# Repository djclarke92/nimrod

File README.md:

# Nimrod Home Automation

A home automation project based on the Raspberry Pi, Modbus IO devices and NodeMCU modules.  The control software is written in C++ and the web configuration is in PHP7.  Relies on 
a MySQL database running on a separate host.  The current software is compiled for Pi model B running the Rasbian buster release.

Why call it Nimrod ?  It needed a name and "Nimrod" was the name of a neanderthal butler in an early Doctor Who episode. The original purpose was to develop something to turn on my
motorbike glove heater 30 minutes before my morning alarm went off if the outside temperature was below 15 deg C.

The Nimrod software is compiled on your standard linux desktop PC, then cross compiled for the Pi version your are using.  In theory you could compile everything on the Pi and 
do away with the cross compiler step.

Uses dygraph.js from http://dygraphs.com for displaying graphs. Websocket support comes from https://libwebsockets.org/.

What can you do with it ?
* Input events can be switches, temperature values, voltage levels or time of day
* Turn on one or more output ports when an input event occurs
* Input switch events can be a click, double click or long click, each can trigger different output actions
* Input events can be chained together, e.g. if time is 6:30am and temperature sensor #2 is < 15 deg then turn on output #7 for 30 minutes
* Complex processes can be managed by the integratd PLC State Machine

Communication with each modbus device is polled.  All digital inputs are active low, i.e. connect to 0V / Gnd to activate.  All digital outputs are active low open collector outputs.

On a Pi4, we recommend that you move the /var file system onto a USB3 hard drive otherwise the Pi's uSDHC card will die quite soon due to the number of writes. 

The Nimrod web page also supports displaying CCTV camera images and video streams, to do this you need the mount the CCTV image storage filesystem onto the Pi (edit /etc/fstab and 
create /etc/.smbpwd).  The camera definitions are in the file/site_config.conf file.
1.	/etc/fstab example
	//<SERVER_IP_ADDRESS>/cctv  /cctv   cifs    auto,gid=users,file_mode=0660,dir_mode=0660,iocharset=utf8,credentials=/etc/.smbpwd  0 0
2.	/etc/.smbpwd example, mode must be 0600
	username=<some_user_name>
	password=<some_password>
	domain=YOURSMBWORKGROUP

Note that for each server using a guest account, you may wish to specify an additional share in /etc/samba/smb.conf
thus;

[cctv]
        comment = cctv
        inherit acls = Yes
        path = /cctv
        read only = No
        vfs objects =
[cctv2]
        comment = cctv2
        inherit acls = Yes
        path = /cctv
        read only = No
        vfs objects =

Add a share for each additional server that will connect using the same account. In /etc/fstab, specifiy the new share name for each additional server
//<SERVER_IP_ADDRESS/cctv2, etc

This works around some Windows/samba peculiarities and allows conflict-free file/directory access.

Alternatively, you could use NFS instead, if you aren't using Windows PC's to access the camera files.

## Devices, Device Info and IO Links

Each Modbus interface device is called a "Device" in Nimrod speak.  So a "Device" could be a 16 digital input unit, 8 relay output unit, 8 analog voltage input unit, etc.

Once you have define a device you need to tell Nimrod what each of it's ports is connected to, this is called the "Device Info".  So for a 16DI unit you would setup input channel 1 is 
"Kitchen switch 1", input channel 2 is "Lounge switch 1", etc. The actual connections are determined by the physical cabling between the switch and the Modbus device.  Output devices 
are similarly defined, e.g. 8RO device channel #4 is "Carport Lights".

Now that you have defined the inputs and outputs you need to tell Nimrod how to connect them together.  This is called "IO Links".  E.g. "Kitchen switch 1" links to 
"Carport Lights", and you can also specify if the output is on until the switch is pressed again or automatically turns off after a set time.

## Supported Modbus devices

Modbus RS485 devices from Wellpro and others

* WP3066ADAM		8DS18B20 - 8x DS18B20 temperature inputs
* WP3082ADAM		8AI - 8x 0-20mA / 4-20mA analog inputs
* WP3084ADAM		8VI - 8x 0-10V DC analog inputs
* WP8025ADAM		8RO - 8x relay outputs
* WP8026ADAM		16DI - 16x digital inputs
* WP8027ADAM		16DO - 16x digital outputs
* WP8028ADAM		8DI/8DO - 8x digital outputs, 8x digital inputs
* PD3064			8KT - 8 K Thermocouples
* HDL300			Submersible water level sensor

## Supported WiFi devices

* NodeMCU (ESP8266)
	modules - adc crypto enduser_setup file gpio http net node pwm tmr uart websocket wifi + TLS

# Nimrod package file structure
* ./LICENSE							GNU v3 license
* ./README.md						This file
* ./RELEASE-NOTES.TXT				A history of changes to Nimrod
* ./index.php						Nimrod web portal home page
* ./favicon.ico						Favicon file
* ./bin/nimrod						Nimrod server executable (amd64)
* ./bin/nimrod-arm7					Nimrod server executable (arm7)
* ./bin/set-address					Set the Modbus device index (amd64)
* ./bin/set-address-arm7			Set the Modbus device index (arm7)
* ./files/cameras.php				Shows CCTV camera snapshots on the Nimrod web console
* ./files/class.email.php
* ./files/common.php				Base configuration and some common functions
* ./files/commonhtml.php			Common functions which include HTML output.
* ./files/deviceinfo.php
* ./files/devices.php
* ./files/dygraph.js				Javascript graphing lib
* ./files/dygraph.css				Javascript graphing lib
* ./files/dygraph.min.js			Javascript graphing lib
* ./files/events.php				ToDo
* ./files/home.php
* ./files/intro.php					What is Nimrod
* ./files/monitor.php				Full screen monitor pages 1 and 2
* ./files/iolinks.php
* ./files/site_config.php
* ./files/site_config.php.sample	Example site config file
* ./files/styles.css
* ./images/*						Various image files to make Nimrod look good
* ./scripts/tables.sql				MySQL table creation sql script
* ./scripts/build-num.sh			Update the build number automatically each time makerelease.sh is run
* ./scripts/makerelease.sh			Create a new nimrod package
* ./scripts/nimrod.service			Exampe Nimrod service file of the Pi
* ./scripts/archive_cctv.sh			Script to delete old cctv files
* ./sounds/alerts.mp3
* ./sounds/warning1.mp3
* ./cctv -> /var/cctv				Symlink to your cctv images storage directory
* ./uploads							Create this directory manually and change the owner:group to www-data:www-data

# Raspberry Pi Model 4

## Create Pi bootable SD card

We recommend 16GB SD cards are used, an 8GB card is likely to run out of space in the future.

1.	umount /dev/sdd1
2.	dd bs=4M if=2019-07-10-raspbian-buster.img of=/dev/sdd
3.	boot the pi
	
## Initial Setup of the Pi

- Menu - Pi Configuration
	- System Tab
	- Expand Filesystem
	- Change password for pi user to something new (default is raspberry, nimrod default is passw0rd.23)
	- set hostname to nimrod (or nimrod2, nimrod3, etc)
	- Disable auto login 
- Interfaces Tab
	- Enable SSH
- Localization
	- Set Locale to EN / NZ
	- Set Timezone to Pacific/Auckland
	- Set Keyboard to United States / English International
	- Set WiFi Country to NZ
- Reboot
- Set password for root > sudu su; passwd
- Set static IP address
- sudo vi /etc/dhcpcd.conf (add to the end of the file)
		interface eth0
	  		static ip_address=192.168.1.199/24
	  		static routers=<your_gateway_ip_address>	
	  		static domain_name_servers=<dns_ip_addres_1> <dns_ip_address_2>
	  			(NZ InspireNet DNS servers are 203.114.168.2 203.114.128.2)
- Reboot	
- apt-get update
- apt-get upgrade
- Reboot

## Create the nimrod user on the Pi

It is recommended that you use the same uid/gid for each user/group across your installation. The useradd/groupadd 
commands have options for this.

1.	> adduser nimrod
	- Set password to something
2.	Add nimrod user to the dialout group to give acces to the /dev/ttyUSB* devices
	> adduser nimrod dialout
3.	Add any public ssh keys to $HOME/.ssh/authorized_keys
4.	Create pub/priv key pair
	> ssh-keygen -t rsa
	- copy the public key to nimrod@<database_server>:~/.ssh/authorized_keys

## Install additional packages required by Nimrod on the Pi

- cmd line: sudo apt-get update (update list of available packages)
- gui: sudo aptitude
- example to install curl
	- apt-cache search curl
	- apt-get install curl

Raspbian buster
- apache2 php.8.x-fpm php php-mysql php-gd
- libmodbus5 libmodbus-dev
- libssl-dev libusb-dev ntpddate
- mariadb-server
- mariadb-client libmariadb-dev
- (old mysql-client libmysqlclient-dev)
- msmtp msmtp-mta mailutils
- libwebsockets8 libwebsockets-dev libwebsockets-test-server
- gparted vsftpd

- Secure the mariadb installation
> sudo mysql_secure_installation

- Enable mod-ssl in apache using a self signed certificate
> sudo a2enmod ssl
> sudo a2ensite default-ssl
> sudo systemctl restart apache2

- Remove the default index.html file
> sudo rm /var/www/html/index.html

- make apache a member of the nimrod group
> sudo adduser www-data nimrod

## remove the swap file from the SD card

> sudo dphys-swapfile swapoff
> sudo dphys-swapfile uninstall
> sudo update-rc.d dphys-swapfile remove

## Move the /var directory onto a USB3 drive

- Once you transfer /var onto the USB3 drive the Pi will not boot without the USB3 drive connected
- Don't try and connect a second USB drive, the Pi4 can't cope with that
- Connect and the USB3 drive, format a large ext4 partition and a smaller swap partition
> sudo gparted

- Get the partition uuid's
> sudo blkid /dev/sda1
> sudo blkid /dev/sda2

- Edit the /etc/fstab to add in the new partitions
> sudo vi /etc/fstab
  # /dev/sda1
  PARTUUID=9ee98a25-97e4-xxxx-xxxx-dd0a23e1f247   swap    swap    defaults        0       0
  # /dev/sda2
  PARTUUID=51b819e6-8fd1-xxxx-xxxx-7ffbb871917e   /var    ext4    defaults        0       2
  
- Mount the new var partition and copy the files across
> sudo mount /dev/sda2 /mnt
> sudo rsync -axov /var/* /mnt

- Reboot and your /var partition and swap are on the USB3 drive
> sudo reboot

## Setup msmtp mail on the Pi

> sudo vi /etc/msmtprc
	# Set default values for all following accounts.
	defaults
	logfile /var/tmp/msmtp.log

	# Use the mail submission port 587 instead of the SMTP port 25.
	port 465

	# Always use TLS.
	tls on
	tls_starttls off

	# Set a list of trusted CAs for TLS. The default is to use system settings, but
	# you can select your own file.
	tls_trust_file /etc/ssl/certs/ca-certificates.crt

	# If you select your own file, you should also use the tls_crl_file command to
	# check for revoked certificates, but unfortunately getting revocation lists and
	# keeping them up to date is not straightforward.
	#tls_crl_file ~/.tls-crls

	# Mail account
	# TODO: Use the users username, e.g. root for system and pi for your raspbian user
	account pi

	# Host name of the SMTP server
	# TODO: Use the host of your own mail account
	host <your_isp_mail_host>

	# As an alternative to tls_trust_file/tls_crl_file, you can use tls_fingerprint
	# to pin a single certificate. You have to update the fingerprint when the
	# server certificate changes, but an attacker cannot trick you into accepting
	# a fraudulent certificate. Get the fingerprint with
	# $ msmtp --serverinfo --tls --tls-certcheck=off --host=smtp.freemail.example
	#tls_fingerprint 00:11:22:33:44:55:66:77:88:99:AA:BB:CC:DD:EE:FF:00:11:22:33
	
	# Envelope-from address
	# TODO: Use your own mail address
	from <pi_hostname>@<your_domain>
	
	# Authentication. The password is given using one of five methods, see below.
	auth on
	
	# TODO: Use your own user name for the mail account
	user pi@<your_domain>
	
	# Password method 1: Add the password to the system keyring, and let msmtp get
	# it automatically. To set the keyring password using Gnome's libsecret:
	# $ secret-tool store --label=msmtp \
	#   host smtp.freemail.example \
	#   service smtp \
	#   user joe.smith
	
	# Password method 2: Store the password in an encrypted file, and tell msmtp
	# which command to use to decrypt it. This is usually used with GnuPG, as in
	# this example. Usually gpg-agent will ask once for the decryption password.
	#passwordeval gpg2 --no-tty -q -d ~/.msmtp-password.gpg
	
	# Password method 3: Store the password directly in this file. Usually it is not
	# a good idea to store passwords in plain text files. If you do it anyway, at
	# least make sure that this file can only be read by yourself.
	# TODO: Use the password of your own mail account
	password <email_password>
	
	# Password method 4: Store the password in ~/.netrc. This method is probably not
	# relevant anymore.
	
	# Password method 5: Do not specify a password. Msmtp will then prompt you for
	# it. This means you need to be able to type into a terminal when msmtp runs.
	
	# Set a default account
	# TODO: Use the same account you've configured under account, e.g. root or pi
	account default: pi
	
	# Map local users to mail addresses (for crontab)
	aliases /etc/aliases
	
> sudo chown pi:pi /etc/msmtprc
> sudo chmod 0600 /etc/msmtprc
> sudo chmod 0777 /var/tmp
  cp /etc/msmtprc ~/.msmtprc

> sudo vi /etc/aliases
	root: pi@<your_domain>
	default: pi@<your_domain>
	
> sudo vi /etc/mail.rc
	set sendmail="/usr/bin/msmtp -t"

## Create a certificate so NodeMCU (ESP8266) WiFi devices can connect

> ssh nimrod@nimrod
> openssl req -x509 -nodes -days 3650 -newkey rsa:2048 -keyout nimrod-cert.key -out nimrod-cert.pem

# MySQL Database server

The MySQL database will contain the nimrod configuration and record events and monitoring data.
1.	Create nimrod user with password
2.	Create pub/priv key
	> ssh-keygen -t rsa
3.	Copy pub key to nimrod@pi
4.	Create nimrod database
5.	Create the nimrod tables
	
## Database username and password

If you want to change the default database username or password you need to edit the tables.sql and files/site_config.php files
to specify your required username and password before you create the tables. 
File:	./files/site_config.php			defines DB_USER_NAME and DB_PASSWORD
File:	./scripts/tables.sql			grant select,insert,update,delete on .......
	
## Database ssh tunnel

Nimrod sets up a tunnel to a remote mysql server as per the IP address in the site_config.php file. On the remote mysql host you need to add nimrod as a user and add 
the ssh keys for all nimrod hosts

# Installing Nimrod on the Pi into /var/www/html for the first time

1.	Copy the install tar file from your PC to the Pi
> scp nimrod-x.y.z.tgz nimrod@nimrod:/var/www/html/.
		
2.	Set permissions and untar the package as the nimrod user
> ssh nimrod@nimrod  
> sudo chown -R nimrod:nimrod /var/www/html  
> cd /var/www/html  
> tar xvzf nimrod.x.y.z.tgz  
> cp files/site_config.php.sample files/site_config.php  
> vi site_config.php  
	- set REMOTE_MYSQL_HOST and DB_PASSWORD
	
3.	Establish the SSH tunnel to the database host to accept the host key as the nimrod user
> ssh nimrod@REMOTE_DB_HOST  
> yes  
> ctrl-d		

4.	Create the guest user for camera ftp login
> adduser guest  
	- Set password to something (cameras will use guest/pwd to ftp videos to the server)
> add cctv symlink
	sudo su - guest
	cd /home/guest
	sudo mkdir /var/cctv .
	sudo mkdir /var/cctv/<camera_name>
	sudo chown -R guest:guest /var/cctv

4.	Apache2 setup
> Create the cctv symlink  
	cd /var/www/html  
	sudo ln -s /var/cctv cctv  
> Add apache to the guest group  
	sudo adduser www-data guest  
> Restart apache  
	sudo service apache2 restart

5.	Move the nimrod.log file onto /var/tmp
> cd /home/nimrod  
> sudo ln -s /var/tmp log  
> sudo vi /var/www/html/files/site_config.php
			
6.	Add nimrod to the guest group
> sudo adduser nimrod guest

7. create the web uploads directory
> sudo mkdir /var/www/html/uploads  
> sudo chown -R nimrod:nimrod /var/www/html  
> sudo chmod g+w /var/www/html/uploads

8.	Set nimrod to start automatically
> ssh pi@nimrod  
> cd /var/www/html  
> sudo cp scripts/nimrod.service.arm(7 or 64) /lib/systemd/system/nimrod.service  
> sudo chown root:root /lib/systemd/system/nimrod.service  
> sudo systemctl enable nimrod.service  
> sudo systemctl start nimrod

9.	Setup vsftpd if you have cameras attached so nimrod and apache can view the video files
> sudo vi /etc/vsftpd.conf  
  write_enable=YES  
  local_umask=002  
> sudo vi /home/guest/.bashrc  
  umask 002
  sudo systemctl restart vsftpd

10.	Nimrod should now be running

See the log in /home/nimrod/nimrod.log.  Point your browser to https://nimrod/index.php
	
11. Add a crontab entry for the nimrod user to archive old cctv files

> 20 4 * * * /home/nimrod/bin/archive_cctv.sh 2>&1

#Installing a signed ssl cert for apache2

See https://peppe8o.com/use-lets-encrypt-and-certbot-to-secure-raspberry-pi-hosted-websites-automatically/ for details
This gives you a 3 month signed certificate

> sudo apt update  
> sudo apt install snapd  
> sudo reboot  
> sudo snap install core  s
> sudo snap refresh core

># remove certbot if it is already installed
> sudo apt remove certbot

> sudo snap install --classic certbot  
> sudo ln -s /snap/bin/certbot /usr/bin/certbot  
> sudo certbot --apache -d <your_domain_name> -d www.<your_domain_name>

To renew the certificate use the following command
> sudo certbot renew

# Setup the cross compiler environment on your linux desktop PC

On your linux desktop PC:
> cd $HOME  
> mkdir raspberrypi  
> cd raspberrypi  
> rsync -rl --delete-after --copy-unsafe-links --progress pi@nimrod:/{lib,usr} $HOME/raspberrypi/rootfs

# Download the raspberrypi tools from github

cd $HOME/raspberrypi

> git clone https://github.com/raspberrypi/tools

# Download the raspberrypi documentation from github 

> git clone https://github.com/raspberrypi/documentation

- add to .bashrc
export PATH=$PATH:$HOME/raspberrypi/tools/arm-bcm2708/gcc-linaro-arm-linux-gnueabihf-raspbian/bin
	
Add gcc/g++ compiler packages to your desktop including 32bit gcc support packages, lib32gcc-6-dev, lib32z1

# Development and debugging

1.	A fairly verbose log file is written to /home/nimrod/nimrod.log
2.	Check the apache2 logs at /var/log/apache/error.log
3.	The nimrod application will automatically upgrade itself if it sees a nimrod.x.y.x.tgz package file in the /var/www/html directory
	To turn off the automatic upgrade feature, touch the file /var/www/html/no.upgrade
4.	The nimrod application will attempt to create an SSH tunnel to the remote MySQL database host on startup.
	To disable the SSH tunnel, touch the file /var/www/html/no.tunnel
5.	Each modbus device must be set with a unique address (1-254) using the set-address (or set-addres-arm7) tool. 
	A maximum of 254 devices are currently supported across any number of Pi's.  
	The baud rate for each modbus device should be set to 19200, the default is 9600, using the set-address tool.
6.	To build the software run the following command
	> ./scripts/makerelease.sh x.y.z ["nimrod_host1 [nimrod_host2]"] [copy]
	where "x.y.z" is the version number you are building,
	 	"nimrod_host1 nimrod_host2" is an optional space separated list of hosts to scp the successful package file onto,
	 	"copy" will just scp the existing package file, skipping the compile step

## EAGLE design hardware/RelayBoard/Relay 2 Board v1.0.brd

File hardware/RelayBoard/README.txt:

2 channel relay board with active low TTL level inputs and 10A relay output for switching 12VDC loads

Fits inside a standard electrical double junction box

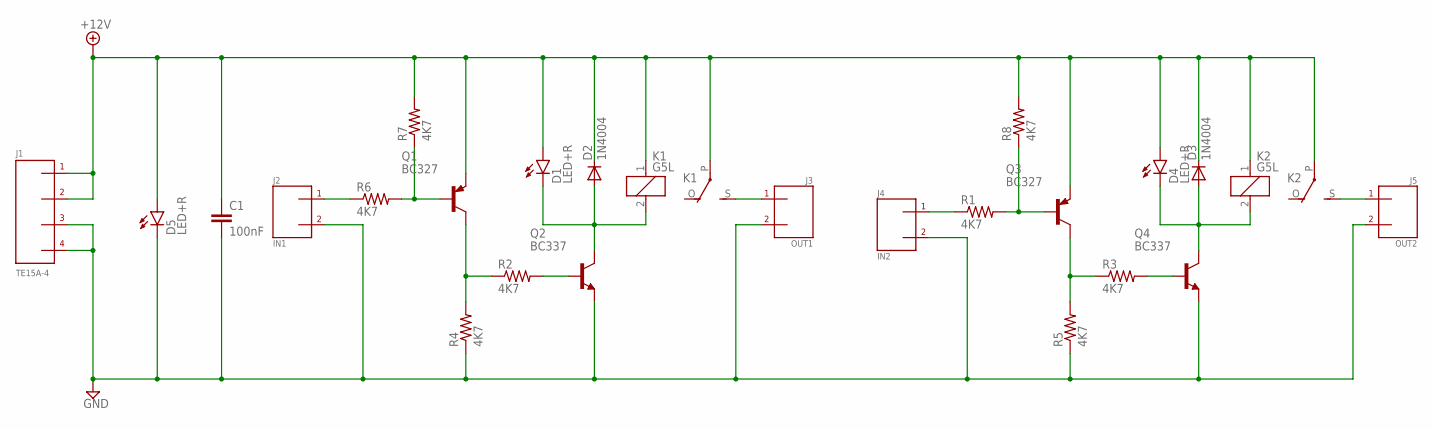
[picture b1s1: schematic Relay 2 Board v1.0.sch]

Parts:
C1: 100nF; CAP-PTH-5MM
D1, D4, D5: LED+R; LED3MM
D2, D3: 1N4004; DO41-10
J1: TE15A-4; J4-950MM
J2: IN1; J2V-508MM
J3: OUT1; J2V-508MM
J4: IN2; J2V-508MM
J5: OUT2; J2V-508MM
K1, K2: G5L; G5LE
Q1, Q3: BC327; TO92
Q2, Q4: BC337; TO92
R1, R2, R3, R4, R5, R6, R7, R8: 4K7; AXIAL-0.3

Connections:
+12V: C1.1, D1.A, D2.C, D3.C, D4.A, D5.A, J1.P$1 (1), J1.P$2 (2), K1.1, K1.P, K2.1, K2.P, Q1.1 (E), Q3.1 (E), R7.P$2 (2), R8.P$2 (2)
GND: C1.2, D5.K (C), J1.P$3 (3), J1.P$4 (4), J2.P$2, J3.P$2, J4.P$2, J5.P$2, Q2.1 (E), Q4.1 (E), R4.P$1 (1), R5.P$1 (1)
unnamed: Q3.2 (B), R1.P$2 (2), R8.P$1 (1)
unnamed: D1.K (C), D2.A, K1.2, Q2.3 (C)
unnamed: Q2.2 (B), R2.P$2 (2)
unnamed: Q1.3 (C), R2.P$1 (1), R4.P$2 (2)
unnamed: J5.P$1, K2.S
unnamed: Q1.2 (B), R6.P$2 (2), R7.P$1 (1)
unnamed: J2.P$1, R6.P$1 (1)
unnamed: J3.P$1, K1.S
unnamed: Q4.2 (B), R3.P$2 (2)
unnamed: Q3.3 (C), R3.P$1 (1), R5.P$2 (2)
unnamed: J4.P$1, R1.P$1 (1)
unnamed: D3.A, D4.K (C), K2.2, Q4.3 (C)

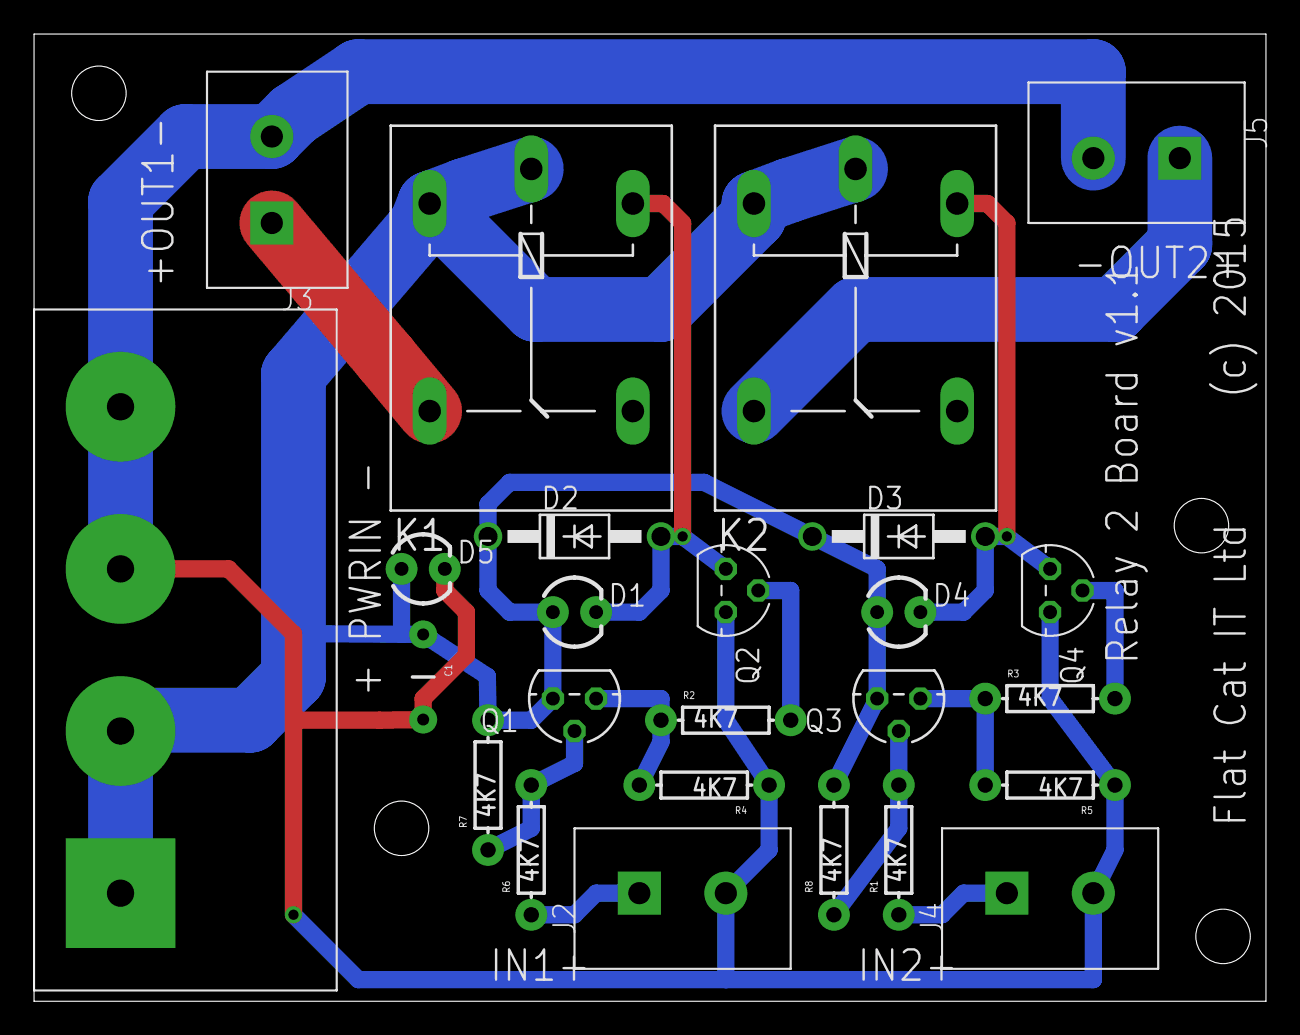
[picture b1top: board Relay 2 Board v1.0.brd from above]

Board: 2 copper layers, 72.4 x 56.8 mm, 25 parts (0 on the bottom side), 14 nets.

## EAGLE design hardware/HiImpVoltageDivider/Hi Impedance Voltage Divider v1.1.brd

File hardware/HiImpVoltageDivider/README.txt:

PCB and SCH files are in Eagle 7.7.0 format

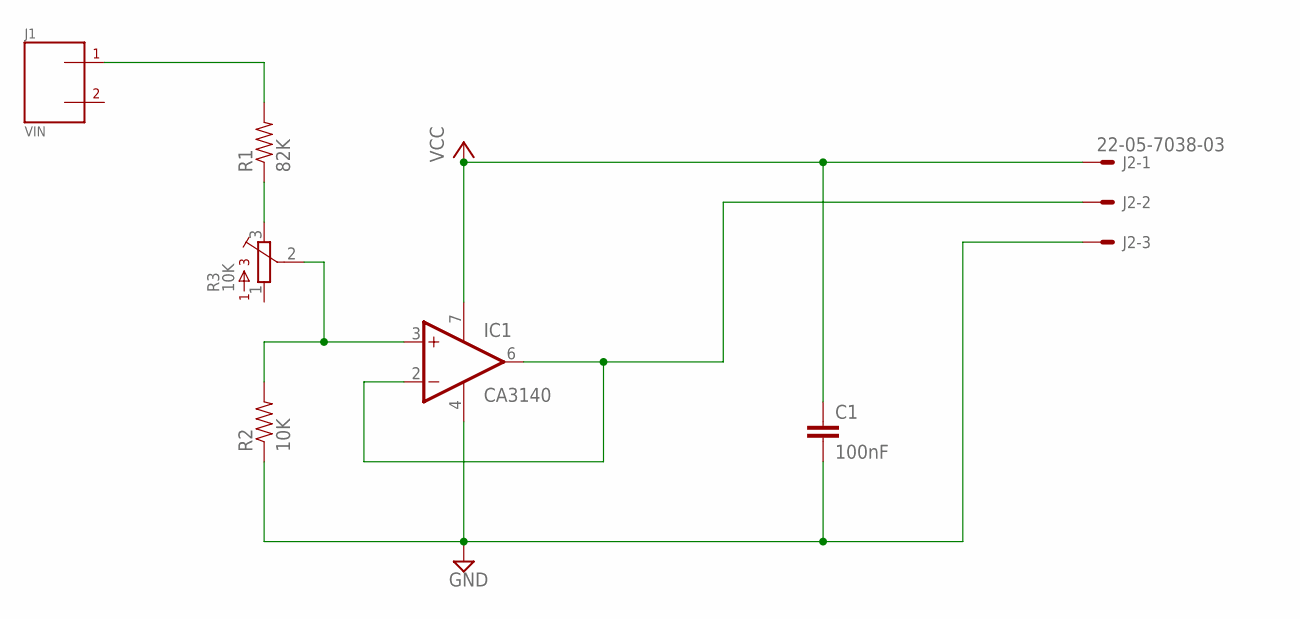
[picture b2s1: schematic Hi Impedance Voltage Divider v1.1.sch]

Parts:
C1: 100nF; CAP-PTH-5MM
IC1: CA3140; DIL08
J1: VIN; J2-508MM
J2: 22-05-7038-03; 7395-03
R1: 82K; AXIAL-0.3
R2: 10K; AXIAL-0.3
R3: 10K; 3386W

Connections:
GND: C1.2, IC1.4 (V-), J2.3, R2.P$1 (1)
unnamed: J1.P$1, R1.P$2 (2)
unnamed: R1.P$1 (1), R3.3
unnamed: IC1.3 (+IN), R2.P$2 (2), R3.2
unnamed: IC1.2 (-IN), IC1.6 (OUT), J2.2
VCC: C1.1, IC1.7 (V+), J2.1

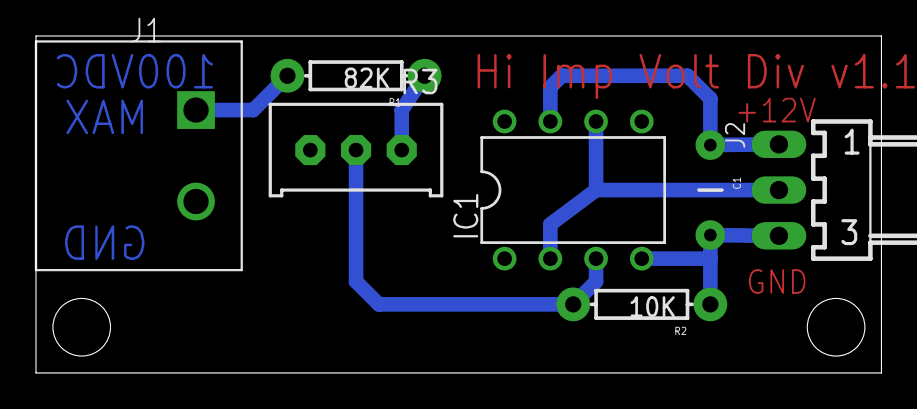
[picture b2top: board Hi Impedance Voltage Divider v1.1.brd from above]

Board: 2 copper layers, 47.0 x 18.7 mm, 7 parts (0 on the bottom side), 6 nets.

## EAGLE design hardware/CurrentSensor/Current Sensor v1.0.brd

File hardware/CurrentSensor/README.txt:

PCB and SCH files are in Eagle 7.7.0 format.

Hall effect current sensor used is WCS1600/1700/1800 depending on max current.  Output from the sensor
is 0 - 5V signal with the 0 Amp poinxit at 2.5V

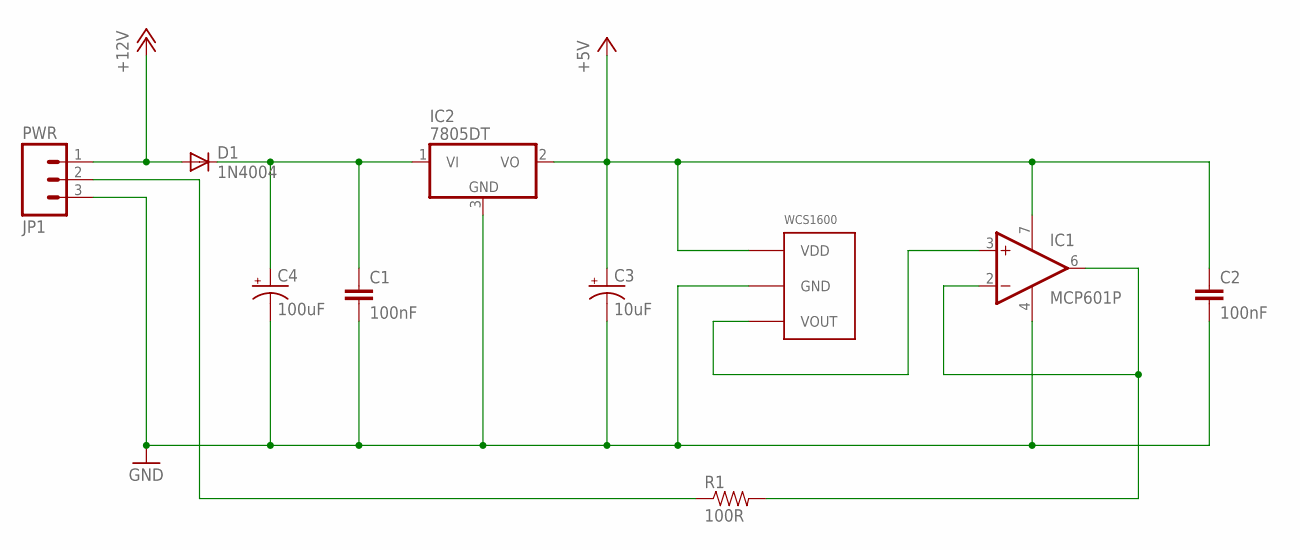
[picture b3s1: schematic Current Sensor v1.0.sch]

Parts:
C1, C2: 100nF; CAP-PTH-SMALL-KIT
C3: 10uF; CPOL-RADIAL-10UF-25V-KIT
C4: 100uF; CPOL-RADIAL-100UF-25V
D1: 1N4004; DO41-10
IC1: MCP601P; DIL08
IC2: 7805DT; TO252
JP1: PWR; MOLEX-1X3
R1: 100R; AXIAL-0.3
U$1: WCSXXXX

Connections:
+5V: C2.1, C3.1 (+), IC1.7 (V+), IC2.2 (VO), U$1.P$1 (VDD)
+12V: D1.A, JP1.1
GND: C1.2, C2.2, C3.2 (-), C4.2 (-), IC1.4 (V-), IC2.3 (GND), JP1.3, U$1.P$2 (GND)
unnamed: IC1.2 (-IN), IC1.6 (OUT), R1.P$2 (2)
unnamed: C1.1, C4.1 (+), D1.C, IC2.1 (VI)
unnamed: JP1.2, R1.P$1 (1)
unnamed: IC1.3 (+IN), U$1.P$3 (VOUT)

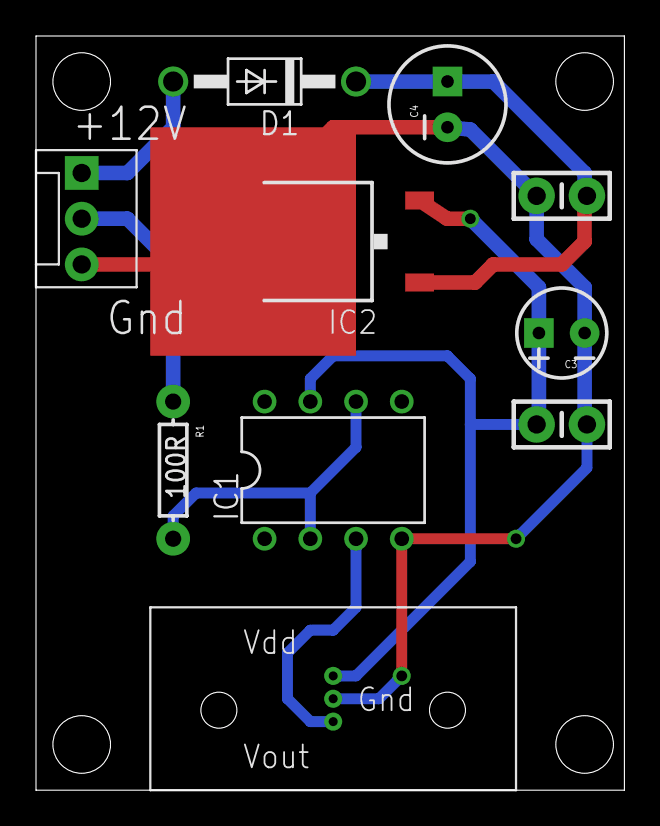
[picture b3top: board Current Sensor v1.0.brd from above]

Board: 2 copper layers, 32.7 x 41.9 mm, 10 parts (0 on the bottom side), 7 nets.

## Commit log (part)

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2019-09-12 Release 0.1.2 supporting Rasbian buster and PHP7
2019-09-12 fix formatting
2019-09-12 add documentation
2019-09-14 Update docs
2019-09-14 Move camera definitions into site_config.conf file, update docs
2019-09-23 Update docs, add NodeMCU code and docs
2019-09-29 Update docs and add hardware PCB and SCH files for HiImpVoltageDivider and CurrentSensor
2019-09-29 Update docs, change web console login
2019-09-30 Added 2 channel relay board BRD and SCH files
2020-07-22 Code changes for release 0.1.3
2020-08-25 Changes for 0.1.4 release
2020-09-16 changes for release 0.1.5
2020-10-27 Changes for release 0.1.6
2020-11-18 Changes for version 0.1.7
2021-05-31 Changes for release 0.1.8
2021-06-05 WIP changes for version 0.2.0
2021-06-09 WIP: changes for 0.2.0
2021-06-13 ESP32 code update
2021-08-16 hanges for versino 0.2.0
2021-10-10 Changes for 0.2.0 release
2021-11-18 Changes for v0.2.1
2022-06-27 Changes for release 0.2.2
2022-06-28 fix bug with initial state of inverted swicth inputs
2022-07-03 Changes for release 0.2.3
2022-07-24 Updates for release 0.2.3
2022-07-25 Final 0.2.3 code changes
2022-08-14 WIP - Changes for release 0.2.4
2022-09-24 WIP: changes for release 0.2.4 '
2022-10-04 WIP: changes for release 0.2.4
2023-02-04 Version 0.2.4 changes
2023-04-23 WIP: release 0.2.5 changes
2023-05-07 WIP: changes for release 0.2.5
2023-09-16 WIP: release 0.2.5
2025-02-22 Final v0.2.5 changes
2025-06-17 release 0.2.6
2025-09-26 WID: 0.2.7 release for weigh bridge
2025-09-27 WIP: 0.2.7
2025-10-06 WIP: weigh bridge changes
2025-10-13 WIP: weigh bridge
2025-11-29 WIP 0.2.7: add systec IT1 support
2025-12-01 WIP: Systec IT1 support
2025-12-12 weigh bridge code
2025-12-12 WIP: weigh bridge printout
2025-12-12 ignore negative weights
2025-12-17 0.2.7 WIP for weigh bridge
2026-01-08 fix bugs in adding new users
2026-01-14 0.2.7: weigh bridge fixes
2026-05-10 WIP: restart camera and set camera time

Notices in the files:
hardware/RelayBoard/Relay 2 Board v1.0.brd:
Flat Cat IT Ltd (c) 2015
parts and their libraries:
SparkFun-Capacitors: Licensing: Creative Commons ShareAlike 4.0 International - https://creativecommons.org/licenses/by-sa/4.0
SparkFun: Licensing: CC v3.0 Share-Alike You are welcome to use this library for commercial purposes.
